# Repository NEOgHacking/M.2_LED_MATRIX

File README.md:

# M.2 LED Matrix

## Description
This is an M.2 compatible LED Matrix board to add an matrix to your desktop PC as a small little display. You can play cool GIFs on this matrix and can control it completely from your PC. This was a speed run done during Kai his ysws speed run. It is made to be as cheep as possible while still being and up to spec M.2 card and uses a 4 layer PCB in the standard 2242 M.2 size. It uses the PCIE protocol to talk to the PC and the PC will be able to send the commands straight to the RP2354 via UART. The RP2354 controls the 11x10 LED matrix and is crammed in on the backside of the PCB.

## Motivation & Idea
I started this project when i was brainstorming in a huddle with allot of people while thinking of ideas for Kai his ysws speedrun. I wanted to create something that would push me a bit and let me learn a bit more about some things but still be doable in 2 days. After some thinking i came up with the beautiful idea to add and LED matrix onto a M.2 card. It would be controlled by a simple microcontroller and it would have a way to interface with the PC it sits in via a protocol over M.2. I settled on the PCIE protocol after a bit of research because it was the one i could get chips for to convert it to UART easily and cheaply, that was one of the other things. This whole project needed to be within budget and that budget isn't big, at $50 it was something to work with. After some researching i found out that the RP2354 was a really cheap microcontroller i could use so i went with that one, also because i know it pretty well.

## Specs
M.2 2242 size
RP2354A microcontroller
CH382L conversion chip
107 LEDs 11x10 matrix
PCIE protocol

## Schematic

## PCB

## BOM

|Reference                                                                                                                                                                                                                                                                                                                                                                                                                                       |Qty|Value        |DNP|Exclude from BOM|Exclude from Board|Exclude from Simulation|Exclude from Position Files|Footprint                                                      |Datasheet                                                                                                                                         |LCSC     |
|------------------------------------------------------------------------------------------------------------------------------------------------------------------------------------------------------------------------------------------------------------------------------------------------------------------------------------------------------------------------------------------------------------------------------------------------|---|-------------|---|----------------|------------------|-----------------------|---------------------------|---------------------------------------------------------------|--------------------------------------------------------------------------------------------------------------------------------------------------|---------|
|C1                                                                                                                                                                                                                                                                                                                                                                                                                                              |1  |100u         |   |                |                  |                       |${EXCLUDE_FROM_POS_FILES}  |Capacitor_Tantalum_SMD:CP_EIA-3528-21_Kemet-B                  |                                                                                                                                                  |C7196    |
|C2,C3                                                                                                                                                                                                                                                                                                                                                                                                                                           |2  |34p          |   |                |                  |                       |${EXCLUDE_FROM_POS_FILES}  |Capacitor_SMD:C_0402_1005Metric                                |                                                                                                                                                  |C70465   |
|C4,C14,C15                                                                                                                                                                                                                                                                                                                                                                                                                                      |3  |10u          |   |                |                  |                       |${EXCLUDE_FROM_POS_FILES}  |Custom:C_Polarized_0805_2012Metric                             |                                                                                                                                                  |C1969735 |
|C5,C6,C7,C9,C10,C11,C12,C13,C16,C26,C28,C29,C30,C31,C32,C33,C34,C36                                                                                                                                                                                                                                                                                                                                                                             |18 |100n         |   |                |                  |                       |${EXCLUDE_FROM_POS_FILES}  |Capacitor_SMD:C_0402_1005Metric                                |                                                                                                                                                  |C1525    |
|C17,C18,C19,C20                                                                                                                                                                                                                                                                                                                                                                                                                                 |4  |1u           |   |                |                  |                       |${EXCLUDE_FROM_POS_FILES}  |Capacitor_SMD:C_0402_1005Metric                                |                                                                                                                                                  |C29266   |
|C21,C22                                                                                                                                                                                                                                                                                                                                                                                                                                         |2  |4u7          |   |                |                  |                       |${EXCLUDE_FROM_POS_FILES}  |Custom:C_0402_1005Metric_small_pads                            |                                                                                                                                                  |C23733   |
|C23,C24                                                                                                                                                                                                                                                                                                                                                                                                                                         |2  |15p          |   |                |                  |                       |${EXCLUDE_FROM_POS_FILES}  |Capacitor_SMD:C_0402_1005Metric                                |                                                                                                                                                  |C1548    |
|C25,C27                                                                                                                                                                                                                                                                                                                                                                                                                                         |2  |4u7          |   |                |                  |                       |${EXCLUDE_FROM_POS_FILES}  |Capacitor_SMD:C_0402_1005Metric                                |                                                                                                                                                  |C23733   |
|D1,D2,D3,D4,D8,D9,D10,D11,D12,D13,D14,D15,D16,D17,D18,D19,D20,D21,D22,D23,D24,D25,D26,D27,D28,D29,D30,D31,D32,D33,D34,D35,D36,D37,D38,D39,D40,D41,D42,D43,D44,D45,D46,D47,D48,D49,D50,D51,D52,D53,D54,D55,D56,D57,D58,D59,D60,D61,D62,D63,D64,D65,D66,D67,D68,D69,D70,D71,D72,D73,D74,D75,D76,D77,D78,D79,D80,D81,D82,D83,D84,D85,D86,D87,D88,D89,D90,D91,D92,D93,D94,D95,D96,D97,D98,D99,D100,D101,D102,D103,D104,D105,D106,D107,D108,D109,D110|107|LED          |   |                |                  |                       |${EXCLUDE_FROM_POS_FILES}  |LED_SMD:LED_0603_1608Metric                                    |                                                                                                                                                  |C965804  |
|L1                                                                                                                                                                                                                                                                                                                                                                                                                                              |1  |3u3          |   |                |                  |                       |${EXCLUDE_FROM_POS_FILES}  |Custom:L_pol_2016                                              |                                                                                                                                                  |C42411119|
|R1                                                                                                                                                                                                                                                                                                                                                                                                                                              |1  |12k          |   |                |                  |                       |${EXCLUDE_FROM_POS_FILES}  |Resistor_SMD:R_0402_1005Metric                                 |                                                                                                                                                  |C2909316 |
|R2                                                                                                                                                                                                                                                                                                                                                                                                                                              |1  |0R           |   |                |                  |                       |${EXCLUDE_FROM_POS_FILES}  |Resistor_SMD:R_0402_1005Metric                                 |                                                                                                                                                  |C106231  |
|R3                                                                                                                                                                                                                                                                                                                                                                                                                                              |1  |33R          |   |                |                  |                       |${EXCLUDE_FROM_POS_FILES}  |Resistor_SMD:R_0402_1005Metric                                 |                                                                                                                                                  |C25105   |
|R4,R7                                                                                                                                                                                                                                                                                                                                                                                                                                           |2  |1k           |   |                |                  |                       |${EXCLUDE_FROM_POS_FILES}  |Resistor_SMD:R_0402_1005Metric                                 |                                                                                                                                                  |C11702   |
|R5,R6                                                                                                                                                                                                                                                                                                                                                                                                                                           |2  |27R          |   |                |                  |                       |${EXCLUDE_FROM_POS_FILES}  |Resistor_SMD:R_0402_1005Metric                                 |                                                                                                                                                  |C2929914 |
|U1                                                                                                                                                                                                                                                                                                                                                                                                                                              |1  |24C02Cx-x-MNY|   |                |                  |                       |${EXCLUDE_FROM_POS_FILES}  |Package_DFN_QFN:DFN-8-1EP_3x2mm_P0.5mm_EP1.36x1.46mm           |https://ww1.microchip.com/downloads/aemDocuments/documents/MPD/ProductDocuments/DataSheets/2-Kbit-5.0V-I2C-Serial-EEPROM-Data-Sheet-DS20001202.pdf|C2061333 |
|U2                                                                                                                                                                                                                                                                                                                                                                                                                                              |1  |AP2112K-3.3  |   |                |                  |                       |${EXCLUDE_FROM_POS_FILES}  |Package_TO_SOT_SMD:SOT-23-5                                    |https://www.diodes.com/assets/Datasheets/AP2112.pdf                                                                                               |C51118   |
|U3                                                                                                                                                                                                                                                                                                                                                                                                                                              |1  |AP2112K-1.8  |   |                |                  |                       |${EXCLUDE_FROM_POS_FILES}  |Package_TO_SOT_SMD:SOT-23-5                                    |https://www.diodes.com/assets/Datasheets/AP2112.pdf                                                                                               |C176944  |
|U4                                                                                                                                                                                                                                                                                                                                                                                                                                              |1  |RP23534A     |   |                |                  |                       |${EXCLUDE_FROM_POS_FILES}  |Package_DFN_QFN:QFN-60-1EP_7x7mm_P0.4mm_EP3.4x3.4mm_ThermalVias|https://datasheets.raspberrypi.com/rp2350/rp2350-datasheet.pdf                                                                                    |C41378174|
|U5                                                                                                                                                                                                                                                                                                                                                                                                                                              |1  |CH382L       |   |                |                  |                       |${EXCLUDE_FROM_POS_FILES}  |Package_QFP:LQFP-64_7x7mm_P0.4mm                               |                                                                                                                                                  |C2685237 |
|Y1                                                                                                                                                                                                                                                                                                                                                                                                                                              |1  |22.1184MHz   |   |                |                  |                       |${EXCLUDE_FROM_POS_FILES}  |Crystal:Crystal_SMD_3225-4Pin_3.2x2.5mm                        |                                                                                                                                                  |C164060  |
|Y2                                                                                                                                                                                                                                                                                                                                                                                                                                              |1  |ABM8-272-T3  |   |                |                  |                       |${EXCLUDE_FROM_POS_FILES}  |Crystal:Crystal_SMD_3225-4Pin_3.2x2.5mm                        |                                                                                                                                                  |C20625731|

## Price
PCB 4L 22x42 ENIG    $18.73 excl shipping

LCSC                 $21.25 excl shipping

jlc shipping&tax     $9.95

LCSC shipping&tax    $21.57

Total                $71.50

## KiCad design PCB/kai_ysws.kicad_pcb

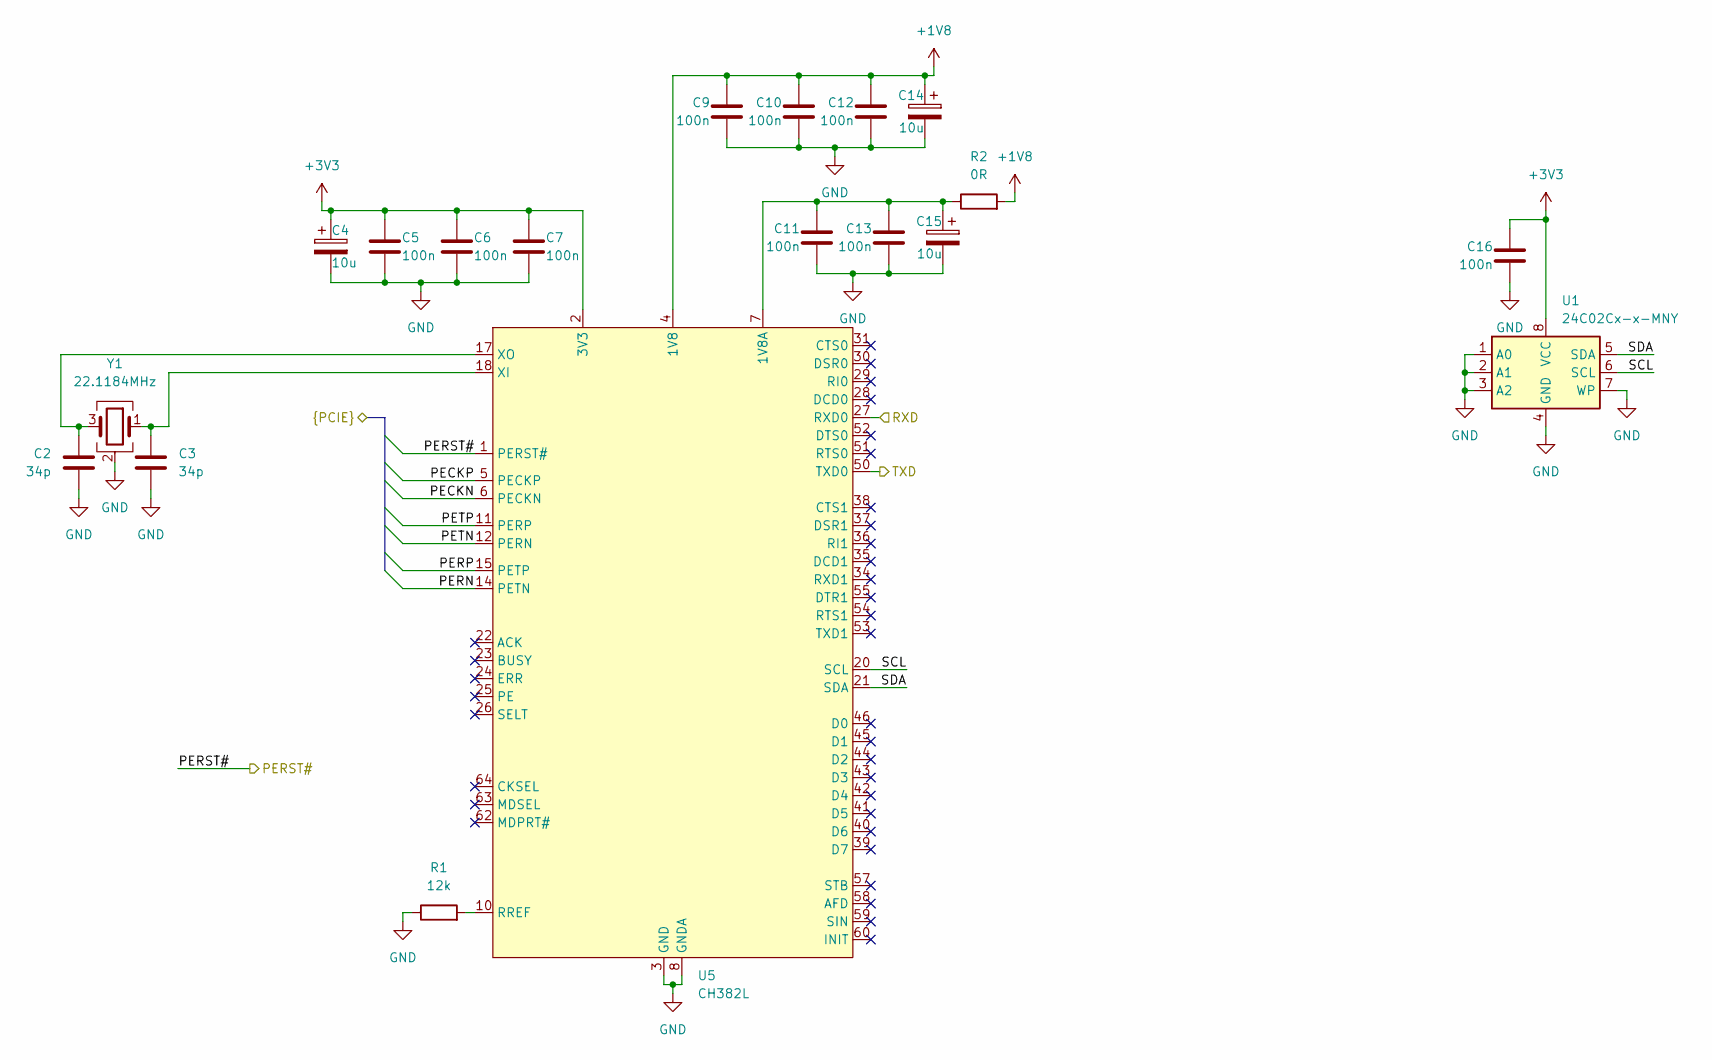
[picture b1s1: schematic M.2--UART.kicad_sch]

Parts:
C2, C3: 34p; C_0402_1005Metric; LCSC C70465
C4, C14, C15: 10u; C_Polarized_0805_2012Metric; LCSC C1969735
C5, C6, C7, C9, C10, C11, C12, C13, C16: 100n; C_0402_1005Metric; LCSC C1525
R1: 12k; R_0402_1005Metric; LCSC C2909316
R2: 0R; R_0402_1005Metric; LCSC C106231
U1: 24C02Cx-x-MNY; DFN-8-1EP_3x2mm_P0.5mm_EP1.36x1.46mm; LCSC C2061333
U5: CH382L; LQFP-64_7x7mm_P0.4mm; LCSC C2685237
Y1: 22.1184MHz; Crystal_SMD_3225-4Pin_3.2x2.5mm; LCSC C164060

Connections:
1V8A: C11.1, C13.1, C15.1, R2.1, U5.7 (1V8A), U5.13 (1V8A)
+1V8: C9.1, C10.1, C12.1, C14.1, R2.2, U5.4 (1V8), U5.32 (1V8), U5.47 (1V8); also elsewhere on the board
+3V3: C4.1, C5.1, C6.1, C7.1, C16.1, U1.8 (VCC), U5.2 (3V3), U5.19 (3V3), U5.49 (3V3); also elsewhere on the board
/M.2 slot/PECKN: U5.6 (PECKN); also elsewhere on the board
/M.2 slot/PECKP: U5.5 (PECKP); also elsewhere on the board
/M.2 slot/PERN: U5.14 (PETN); also elsewhere on the board
/M.2 slot/PERP: U5.15 (PETP); also elsewhere on the board
/M.2 slot/PERST#: U5.1 (PERST#); also elsewhere on the board
/M.2 slot/PETN: U5.12 (PERN); also elsewhere on the board
/M.2 slot/PETP: U5.11 (PERP); also elsewhere on the board
/M.2 to UART/RXD: U5.27 (RXD0); also elsewhere on the board
/M.2 to UART/SCL: U1.6 (SCL), U5.20 (SCL)
/M.2 to UART/SDA: U1.5 (SDA), U5.21 (SDA)
/M.2 to UART/TXD: U5.50 (TXD0); also elsewhere on the board
GND: C2.2, C3.2, C4.2, C5.2, C6.2, C7.2, C9.2, C10.2, C11.2, C12.2, C13.2, C14.2, C15.2, C16.2, R1.1, U1.1 (A0), U1.2 (A1), U1.3 (A2), U1.4 (GND), U1.7 (WP), U1.9 (GND), U5.3 (GND), U5.8 (GNDA), U5.9 (GNDA), U5.16 (GND), U5.33 (GND), U5.48 (GND), U5.56 (GND), U5.61 (GND), Y1.2 (G), Y1.4 (G); also elsewhere on the board
unnamed: R1.2, U5.10 (RREF)
unnamed: C3.1, U5.18 (XI), Y1.1
unnamed: C2.1, U5.17 (XO), Y1.3

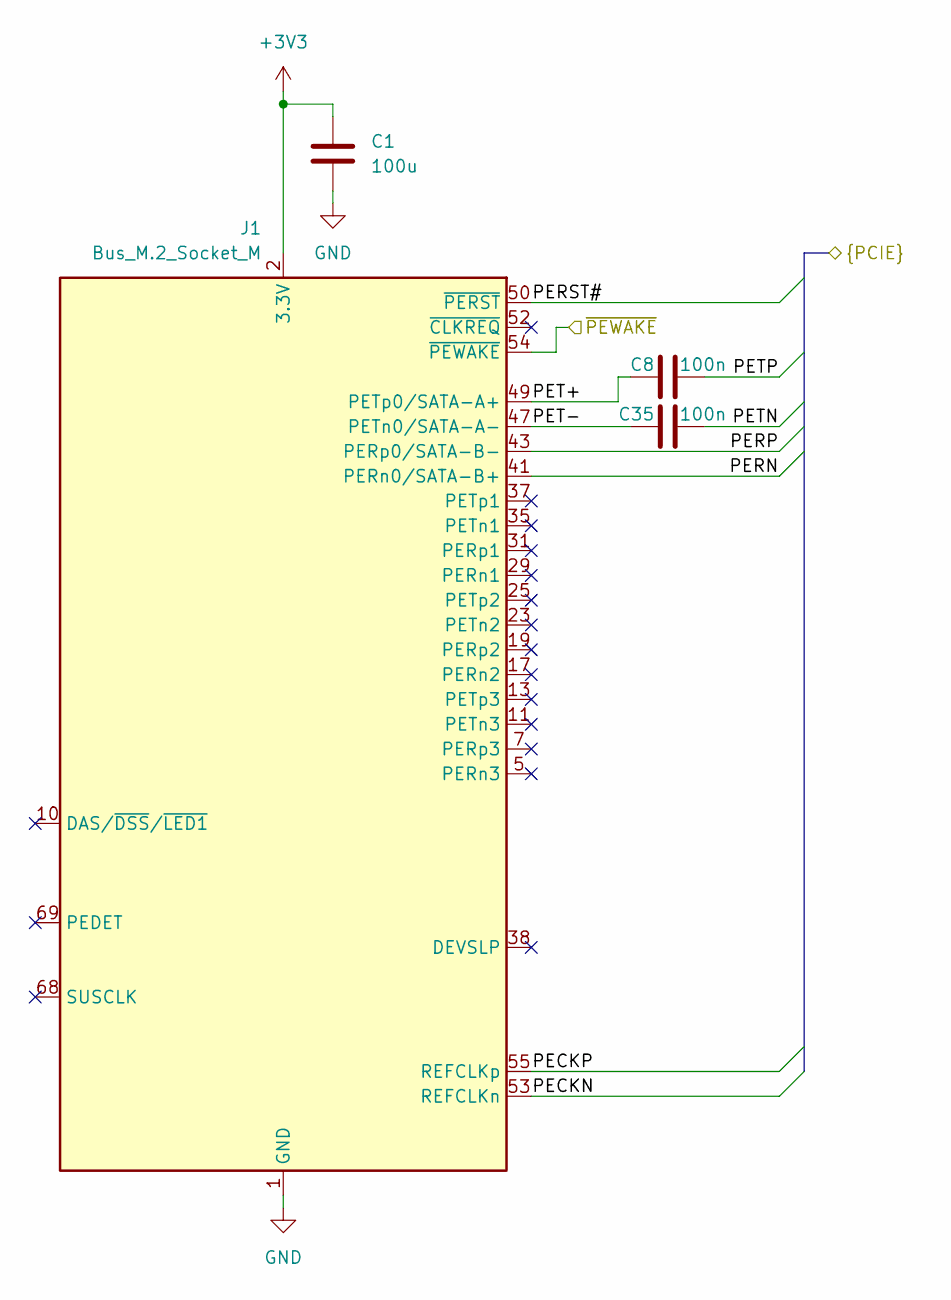
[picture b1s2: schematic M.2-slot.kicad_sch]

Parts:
C1: 100u; CP_EIA-3528-21_Kemet-B; LCSC C7196
C8, C35: 100n; C_0402_1005Metric; LCSC C1525
J1: Bus_M.2_Socket_M; M.2_2242-xx-M

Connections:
+3V3: C1.1, J1.2 (3.3V), J1.4 (3.3V), J1.12 (3.3V), J1.14 (3.3V), J1.16 (3.3V), J1.18 (3.3V), J1.70 (3.3V), J1.72 (3.3V), J1.74 (3.3V); also elsewhere on the board
/M.2 slot/PECKN: J1.53 (REFCLKn); also elsewhere on the board
/M.2 slot/PECKP: J1.55 (REFCLKp); also elsewhere on the board
/M.2 slot/PERN: J1.41 (PERn0/SATA-B+); also elsewhere on the board
/M.2 slot/PERP: J1.43 (PERp0/SATA-B-); also elsewhere on the board
/M.2 slot/PERST#: J1.50 (~PERST); also elsewhere on the board
/M.2 slot/PET+: C8.1, J1.49 (PETp0/SATA-A+)
/M.2 slot/PET-: C35.1, J1.47 (PETn0/SATA-A-)
/M.2 slot/PETN: C35.2; also elsewhere on the board
/M.2 slot/PETP: C8.2; also elsewhere on the board
/M.2 slot/~PEWAKE: J1.54 (~PEWAKE); also elsewhere on the board
GND: C1.2, J1.1 (GND), J1.3 (GND), J1.9 (GND), J1.15 (GND), J1.21 (GND), J1.27 (GND), J1.33 (GND), J1.39 (GND), J1.45 (GND), J1.51 (GND), J1.57 (GND), J1.71 (GND), J1.73 (GND), J1.75 (GND); also elsewhere on the board

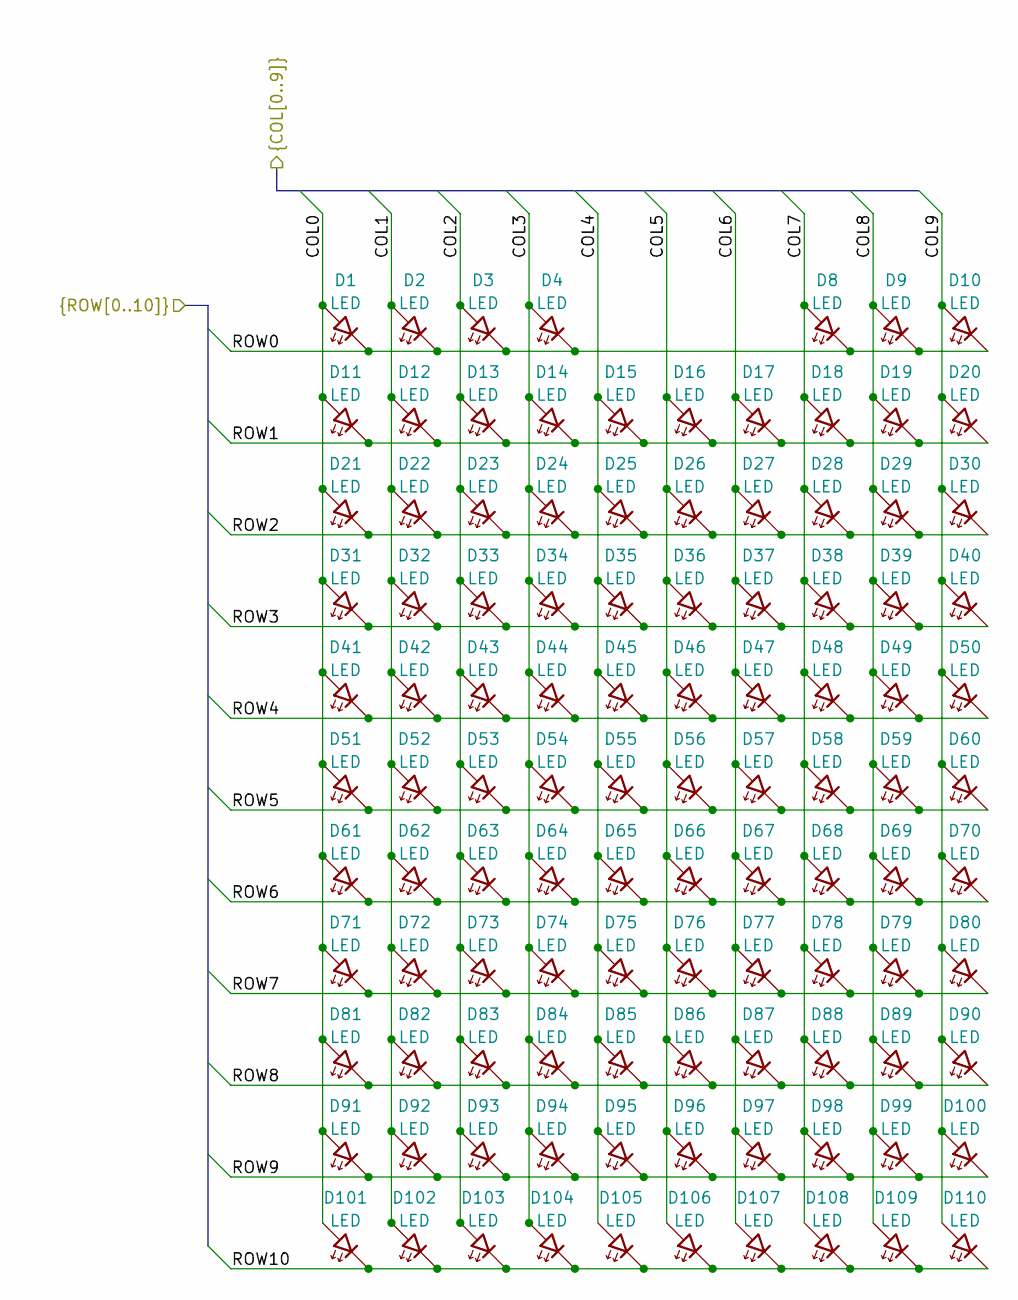
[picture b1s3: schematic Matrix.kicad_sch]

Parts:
D1, D2, D3, D4, D8, D9, D10, D11, D12, D13, D14, D15, D16, D17, D18, D19, D20, D21, D22, D23, D24, D25, D26, D27, D28, D29, D30, D31, D32, D33, D34, D35, D36, D37, D38, D39, D40, D41, D42, D43, D44, D45, D46, D47, D48, D49, D50, D51, D52, D53, D54, D55, D56, D57, D58, D59, D60, D61, D62, D63, D64, D65, D66, D67, D68, D69, D70, D71, D72, D73, D74, D75, D76, D77, D78, D79, D80, D81, D82, D83, D84, D85, D86, D87, D88, D89, D90, D91, D92, D93, D94, D95, D96, D97, D98, D99, D100, D101, D102, D103, D104, D105, D106, D107, D108, D109, D110: LED; LED_0603_1608Metric; LCSC C965804

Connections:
/Matrix/COL0: D1.2 (A), D11.2 (A), D21.2 (A), D31.2 (A), D41.2 (A), D51.2 (A), D61.2 (A), D71.2 (A), D81.2 (A), D91.2 (A), D101.2 (A); also elsewhere on the board
/Matrix/COL1: D2.2 (A), D12.2 (A), D22.2 (A), D32.2 (A), D42.2 (A), D52.2 (A), D62.2 (A), D72.2 (A), D82.2 (A), D92.2 (A), D102.2 (A); also elsewhere on the board
/Matrix/COL2: D3.2 (A), D13.2 (A), D23.2 (A), D33.2 (A), D43.2 (A), D53.2 (A), D63.2 (A), D73.2 (A), D83.2 (A), D93.2 (A), D103.2 (A); also elsewhere on the board
/Matrix/COL3: D4.2 (A), D14.2 (A), D24.2 (A), D34.2 (A), D44.2 (A), D54.2 (A), D64.2 (A), D74.2 (A), D84.2 (A), D94.2 (A), D104.2 (A); also elsewhere on the board
/Matrix/COL4: D15.2 (A), D25.2 (A), D35.2 (A), D45.2 (A), D55.2 (A), D65.2 (A), D75.2 (A), D85.2 (A), D95.2 (A), D105.2 (A); also elsewhere on the board
/Matrix/COL5: D16.2 (A), D26.2 (A), D36.2 (A), D46.2 (A), D56.2 (A), D66.2 (A), D76.2 (A), D86.2 (A), D96.2 (A), D106.2 (A); also elsewhere on the board
/Matrix/COL6: D17.2 (A), D27.2 (A), D37.2 (A), D47.2 (A), D57.2 (A), D67.2 (A), D77.2 (A), D87.2 (A), D97.2 (A), D107.2 (A); also elsewhere on the board
/Matrix/COL7: D8.2 (A), D18.2 (A), D28.2 (A), D38.2 (A), D48.2 (A), D58.2 (A), D68.2 (A), D78.2 (A), D88.2 (A), D98.2 (A), D108.2 (A); also elsewhere on the board
/Matrix/COL8: D9.2 (A), D19.2 (A), D29.2 (A), D39.2 (A), D49.2 (A), D59.2 (A), D69.2 (A), D79.2 (A), D89.2 (A), D99.2 (A), D109.2 (A); also elsewhere on the board
/Matrix/COL9: D10.2 (A), D20.2 (A), D30.2 (A), D40.2 (A), D50.2 (A), D60.2 (A), D70.2 (A), D80.2 (A), D90.2 (A), D100.2 (A), D110.2 (A); also elsewhere on the board
/Matrix/ROW0: D1.1 (K), D2.1 (K), D3.1 (K), D4.1 (K), D8.1 (K), D9.1 (K), D10.1 (K); also elsewhere on the board
/Matrix/ROW1: D11.1 (K), D12.1 (K), D13.1 (K), D14.1 (K), D15.1 (K), D16.1 (K), D17.1 (K), D18.1 (K), D19.1 (K), D20.1 (K); also elsewhere on the board
/Matrix/ROW2: D21.1 (K), D22.1 (K), D23.1 (K), D24.1 (K), D25.1 (K), D26.1 (K), D27.1 (K), D28.1 (K), D29.1 (K), D30.1 (K); also elsewhere on the board
/Matrix/ROW3: D31.1 (K), D32.1 (K), D33.1 (K), D34.1 (K), D35.1 (K), D36.1 (K), D37.1 (K), D38.1 (K), D39.1 (K), D40.1 (K); also elsewhere on the board
/Matrix/ROW4: D41.1 (K), D42.1 (K), D43.1 (K), D44.1 (K), D45.1 (K), D46.1 (K), D47.1 (K), D48.1 (K), D49.1 (K), D50.1 (K); also elsewhere on the board
/Matrix/ROW5: D51.1 (K), D52.1 (K), D53.1 (K), D54.1 (K), D55.1 (K), D56.1 (K), D57.1 (K), D58.1 (K), D59.1 (K), D60.1 (K); also elsewhere on the board
/Matrix/ROW6: D61.1 (K), D62.1 (K), D63.1 (K), D64.1 (K), D65.1 (K), D66.1 (K), D67.1 (K), D68.1 (K), D69.1 (K), D70.1 (K); also elsewhere on the board
/Matrix/ROW7: D71.1 (K), D72.1 (K), D73.1 (K), D74.1 (K), D75.1 (K), D76.1 (K), D77.1 (K), D78.1 (K), D79.1 (K), D80.1 (K); also elsewhere on the board
/Matrix/ROW8: D81.1 (K), D82.1 (K), D83.1 (K), D84.1 (K), D85.1 (K), D86.1 (K), D87.1 (K), D88.1 (K), D89.1 (K), D90.1 (K); also elsewhere on the board
/Matrix/ROW9: D91.1 (K), D92.1 (K), D93.1 (K), D94.1 (K), D95.1 (K), D96.1 (K), D97.1 (K), D98.1 (K), D99.1 (K), D100.1 (K); also elsewhere on the board
/Matrix/ROW10: D101.1 (K), D102.1 (K), D103.1 (K), D104.1 (K), D105.1 (K), D106.1 (K), D107.1 (K), D108.1 (K), D109.1 (K), D110.1 (K); also elsewhere on the board

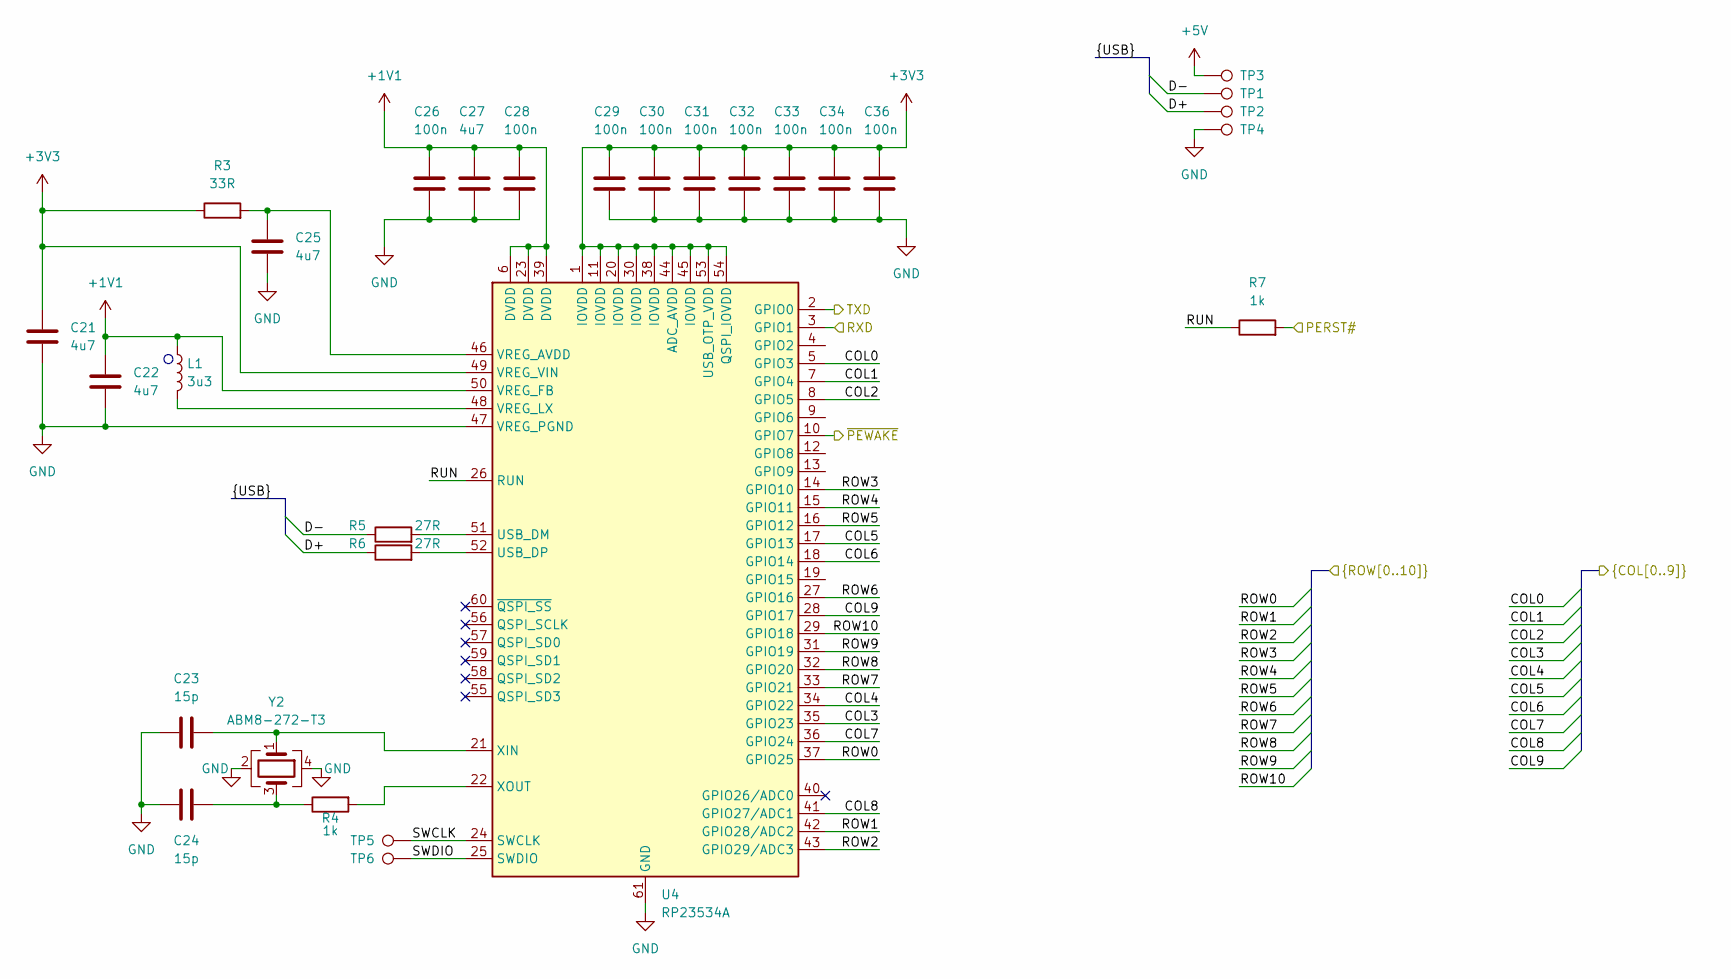
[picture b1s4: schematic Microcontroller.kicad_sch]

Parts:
C21, C22: 4u7; C_0402_1005Metric_small_pads; LCSC C23733
C23, C24: 15p; C_0402_1005Metric; LCSC C1548
C25, C27: 4u7; C_0402_1005Metric; LCSC C23733
C26, C28, C29, C30, C31, C32, C33, C34, C36: 100n; C_0402_1005Metric; LCSC C1525
L1: 3u3; L_pol_2016; LCSC C42411119
R3: 33R; R_0402_1005Metric; LCSC C25105
R4, R7: 1k; R_0402_1005Metric; LCSC C11702
R5, R6: 27R; R_0402_1005Metric; LCSC C2929914
TP1, TP2, TP3, TP4, TP5, TP6: TestPoint; TestPoint_Pad_D1.0mm
U4: RP23534A; QFN-60-1EP_7x7mm_P0.4mm_EP3.4x3.4mm_ThermalVias; LCSC C41378174
Y2: ABM8-272-T3; Crystal_SMD_3225-4Pin_3.2x2.5mm; LCSC C20625731

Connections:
+1V1: C22.1, C26.1, C27.1, C28.1, L1.1, U4.6 (DVDD), U4.23 (DVDD), U4.39 (DVDD), U4.50 (VREG_FB)
+3V3: C21.1, C29.1, C30.1, C31.1, C32.1, C33.1, C34.1, C36.1, R3.1, U4.1 (IOVDD), U4.11 (IOVDD), U4.20 (IOVDD), U4.30 (IOVDD), U4.38 (IOVDD), U4.44 (ADC_AVDD), U4.45 (IOVDD), U4.49 (VREG_VIN), U4.53 (USB_OTP_VDD), U4.54 (QSPI_IOVDD); also elsewhere on the board
+5V: TP3.1 (1_1); also elsewhere on the board
/M.2 slot/PERST#: R7.2; also elsewhere on the board
/M.2 slot/~PEWAKE: U4.10 (GPIO7); also elsewhere on the board
/M.2 to UART/RXD: U4.2 (GPIO0); also elsewhere on the board
/M.2 to UART/TXD: U4.3 (GPIO1); also elsewhere on the board
/Matrix/COL0: U4.5 (GPIO3); also elsewhere on the board
/Matrix/COL1: U4.7 (GPIO4); also elsewhere on the board
/Matrix/COL2: U4.8 (GPIO5); also elsewhere on the board
/Matrix/COL3: U4.35 (GPIO23); also elsewhere on the board
/Matrix/COL4: U4.34 (GPIO22); also elsewhere on the board
/Matrix/COL5: U4.17 (GPIO13); also elsewhere on the board
/Matrix/COL6: U4.18 (GPIO14); also elsewhere on the board
/Matrix/COL7: U4.36 (GPIO24); also elsewhere on the board
/Matrix/COL8: U4.41 (GPIO27/ADC1); also elsewhere on the board
/Matrix/COL9: U4.28 (GPIO17); also elsewhere on the board
/Matrix/ROW0: U4.37 (GPIO25); also elsewhere on the board
/Matrix/ROW1: U4.42 (GPIO28/ADC2); also elsewhere on the board
/Matrix/ROW2: U4.43 (GPIO29/ADC3); also elsewhere on the board
/Matrix/ROW3: U4.14 (GPIO10); also elsewhere on the board
/Matrix/ROW4: U4.15 (GPIO11); also elsewhere on the board
/Matrix/ROW5: U4.16 (GPIO12); also elsewhere on the board
/Matrix/ROW6: U4.27 (GPIO16); also elsewhere on the board
/Matrix/ROW7: U4.33 (GPIO21); also elsewhere on the board
/Matrix/ROW8: U4.32 (GPIO20); also elsewhere on the board
/Matrix/ROW9: U4.31 (GPIO19); also elsewhere on the board
/Matrix/ROW10: U4.29 (GPIO18); also elsewhere on the board
/Microcontroller/D+: R6.1, TP2.1 (1_1)
/Microcontroller/D-: R5.1, TP1.1 (1_1)
/Microcontroller/RUN: R7.1, U4.26 (RUN)
/Microcontroller/SWCLK: TP5.1 (1_1), U4.24 (SWCLK)
/Microcontroller/SWDIO: TP6.1 (1_1), U4.25 (SWDIO)
GND: C21.2, C22.2, C23.1, C24.1, C25.2, C26.2, C27.2, C28.2, C29.2, C30.2, C31.2, C32.2, C33.2, C34.2, C36.2, TP4.1 (1_1), U4.47 (VREG_PGND), U4.61 (GND), Y2.2 (G), Y2.4 (G); also elsewhere on the board
unnamed: C24.2, R4.1, Y2.3
unnamed: R5.2, U4.51 (USB_DM)
unnamed: R6.2, U4.52 (USB_DP)
unnamed: C25.1, R3.2, U4.46 (VREG_AVDD)
unnamed: L1.2, U4.48 (VREG_LX)
unnamed: C23.2, U4.21 (XIN), Y2.1
unnamed: R4.2, U4.22 (XOUT)

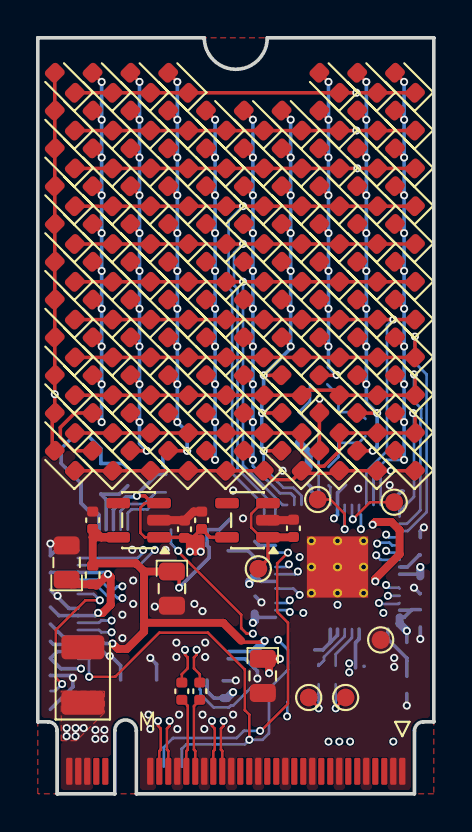
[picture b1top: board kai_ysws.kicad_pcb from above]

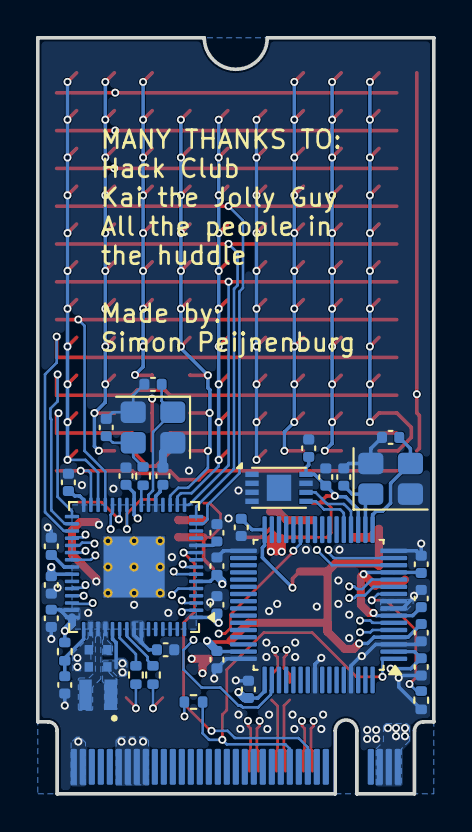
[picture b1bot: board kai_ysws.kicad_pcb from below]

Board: 4 copper layers, 22.0 x 42.0 mm, 165 parts (38 on the bottom side), 56 nets.

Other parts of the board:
C17, C18, C19, C20: 1u; C_0402_1005Metric
U2: AP2112K-3.3; SOT-23-5
U3: AP2112K-1.8; SOT-23-5

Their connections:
+1V8: C20.1, U3.5 (VOUT); also elsewhere on the board
+3V3: C18.1, C19.1, U2.5 (VOUT), U3.1 (VIN), U3.3 (EN); also elsewhere on the board
+5V: C17.1, U2.1 (VIN), U2.3 (EN); also elsewhere on the board
GND: C17.2, C18.2, C19.2, C20.2, U2.2 (GND), U3.2 (GND); also elsewhere on the board

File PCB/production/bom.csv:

Designator,Footprint,Quantity,Value,LCSC Part #
C1,CP_EIA-3528-21_Kemet-B,1,100u,C7196
"C10, C11, C12, C13, C16, C26, C28, C29, C30, C31, C32, C33, C34, C36, C5, C6, C7, C9",0402,18,100n,C1525
"C14, C15, C4",C_Polarized_0805_2012Metric,3,10u,C1969735
"C17, C18, C19, C20",0402,4,1u,
"C2, C3",0402,2,C,
"C21, C22, C25, C27",0402,4,4u7,C23733
"C23, C24",0402,2,15p,C1548
"D1, D10, D100, D101, D102, D103, D104, D105, D106, D107, D108, D109, D11, D110, D12, D13, D14, D15, D16, D17, D18, D19, D2, D20, D21, D22, D23, D24, D25, D26, D27, D28, D29, D3, D30, D31, D32, D33, D34, D35, D36, D37, D38, D39, D4, D40, D41, D42, D43, D44, D45, D46, D47, D48, D49, D50, D51, D52, D53, D54, D55, D56, D57, D58, D59, D60, D61, D62, D63, D64, D65, D66, D67, D68, D69, D70, D71, D72, D73, D74, D75, D76, D77, D78, D79, D8, D80, D81, D82, D83, D84, D85, D86, D87, D88, D89, D9, D90, D91, D92, D93, D94, D95, D96, D97, D98, D99",0603,107,LED,
J1,M.2_2242-xx-M,1,Bus_M.2_Socket_M,
L1,L_pol_2016,1,3u3,C42411119
R1,0402,1,12k,
R2,0402,1,0R,
R3,0402,1,33R,C25105
R4,0402,1,1k,C11702
"R5, R6",0402,2,27R,C2929914
R7,0402,1,1k,
"TP1, TP2, TP3, TP4, TP5, TP6",TestPoint_Pad_D1.0mm,6,TestPoint,
U1,DFN-8-1EP_3x2mm_P0.5mm_EP1.36x1.46mm,1,24C02Cx-x-MNY,
U2,SOT-23-5,1,AP2112K-3.3,C51118
U3,SOT-23-5,1,AP2112K-1.8,C176944
U4,QFN-60-1EP_7x7mm_P0.4mm_EP3.4x3.4mm_ThermalVias,1,RP23534A,C41378174
U5,LQFP-64_7x7mm_P0.4mm,1,CH382L,C2685237
Y1,Crystal_SMD_3225-4Pin_3.2x2.5mm,1,22.1184MHz,C164060
Y2,Crystal_SMD_3225-4Pin_3.2x2.5mm,1,ABM8-272-T3,5A992C
